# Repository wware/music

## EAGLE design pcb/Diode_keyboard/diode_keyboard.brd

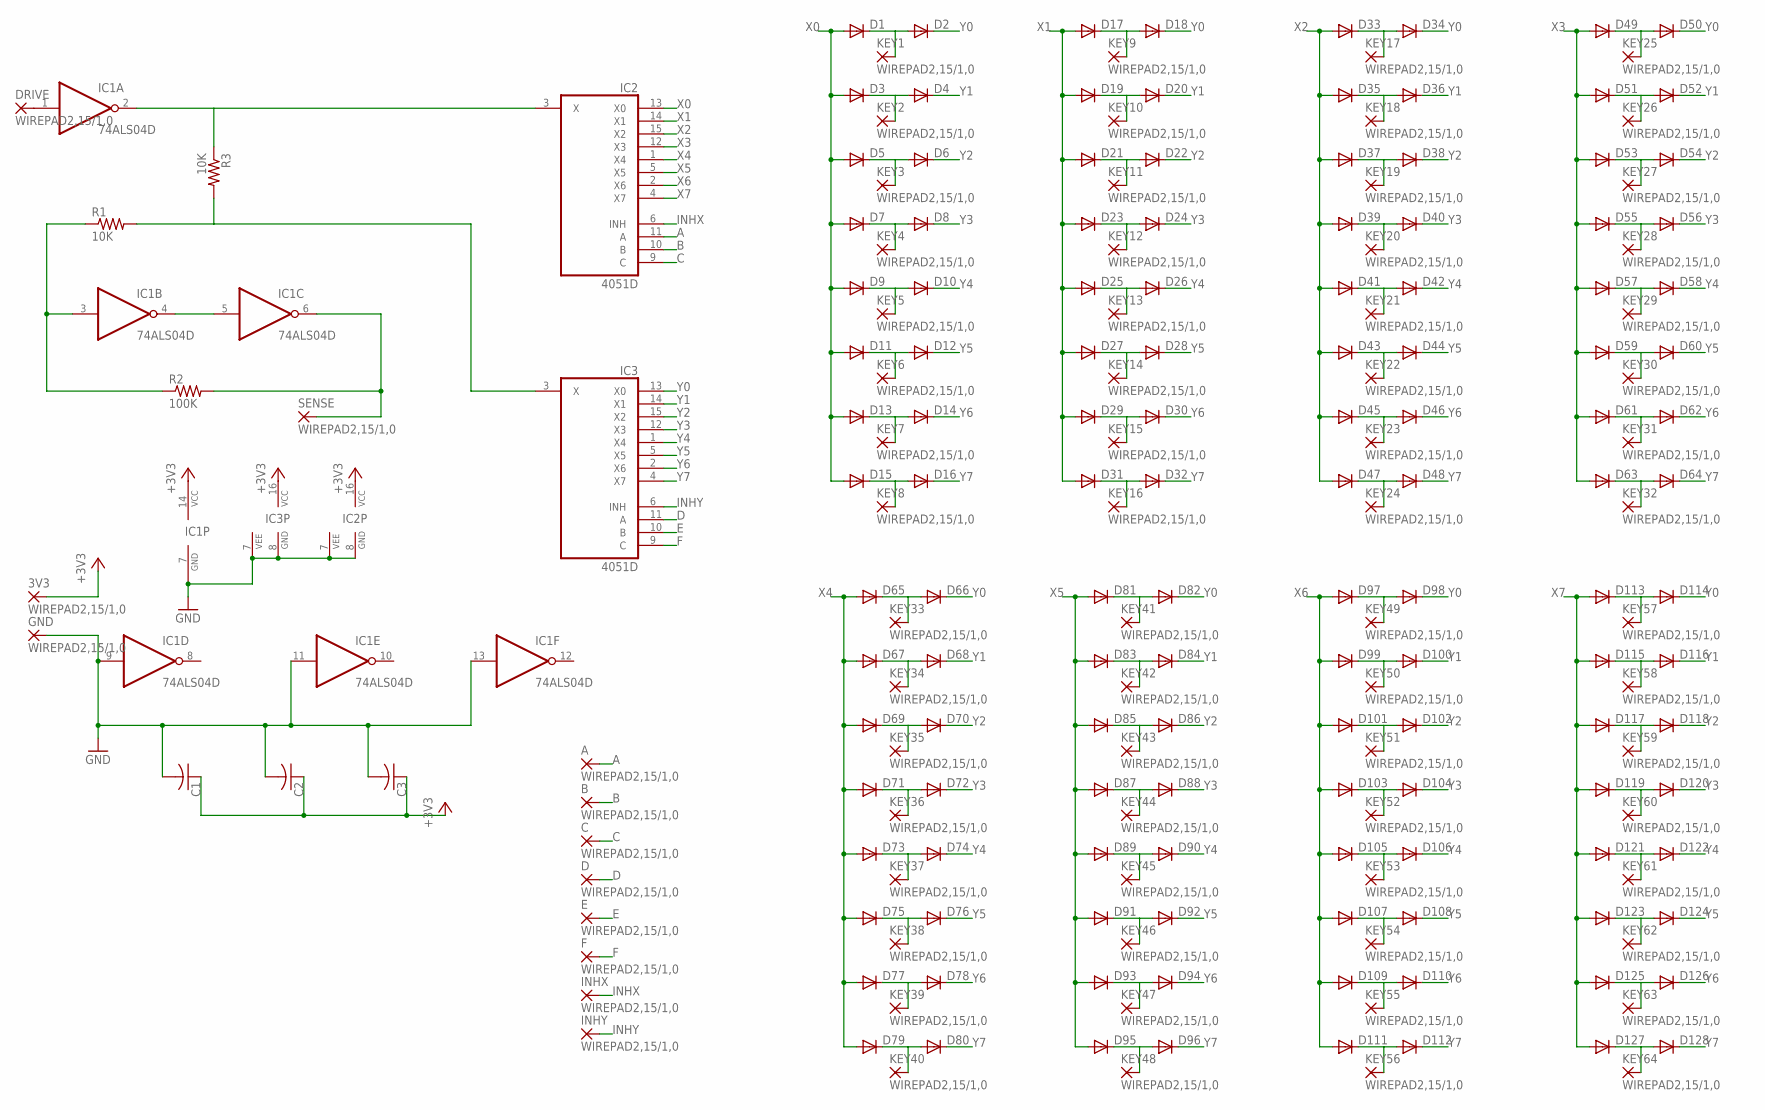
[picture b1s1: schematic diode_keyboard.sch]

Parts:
3V3: WIREPAD2,15/1,0; 2,15/1,0
A: WIREPAD2,15/1,0; 2,15/1,0
B: WIREPAD2,15/1,0; 2,15/1,0
C: WIREPAD2,15/1,0; 2,15/1,0
C1, C2, C3: C-US025-024X044; C025-024X044
D: WIREPAD2,15/1,0; 2,15/1,0
D1, D2, D3, D4, D5, D6, D7, D8, D9, D10, D11, D12, D13, D14, D15, D16, D17, D18, D19, D20, D21, D22, D23, D24, D25, D26, D27, D28, D29, D30, D31, D32, D33, D34, D35, D36, D37, D38, D39, D40, D41, D42, D43, D44, D45, D46, D47, D48, D49, D50, D51, D52, D53, D54, D55, D56, D57, D58, D59, D60, D61, D62, D63, D64, D65, D66, D67, D68, D69, D70, D71, D72, D73, D74, D75, D76, D77, D78, D79, D80, D81, D82, D83, D84, D85, D86, D87, D88, D89, D90, D91, D92, D93, D94, D95, D96, D97, D98, D99, D100, D101, D102, D103, D104, D105, D106, D107, D108, D109, D110, D111, D112, D113, D114, D115, D116, D117, D118, D119, D120, D121, D122, D123, D124, D125, D126, D127, D128: DIODE-D-2.5; D-2.5
DRIVE: WIREPAD2,15/1,0; 2,15/1,0
E: WIREPAD2,15/1,0; 2,15/1,0
F: WIREPAD2,15/1,0; 2,15/1,0
GND: WIREPAD2,15/1,0; 2,15/1,0
IC1: 74ALS04D; SO14
IC2, IC3: 4051D; SO16
INHX: WIREPAD2,15/1,0; 2,15/1,0
INHY: WIREPAD2,15/1,0; 2,15/1,0
KEY1, KEY2, KEY3, KEY4, KEY5, KEY6, KEY7, KEY8, KEY9, KEY10, KEY11, KEY12, KEY13, KEY14, KEY15, KEY16, KEY17, KEY18, KEY19, KEY20, KEY21, KEY22, KEY23, KEY24, KEY25, KEY26, KEY27, KEY28, KEY29, KEY30, KEY31, KEY32, KEY33, KEY34, KEY35, KEY36, KEY37, KEY38, KEY39, KEY40, KEY41, KEY42, KEY43, KEY44, KEY45, KEY46, KEY47, KEY48, KEY49, KEY50, KEY51, KEY52, KEY53, KEY54, KEY55, KEY56, KEY57, KEY58, KEY59, KEY60, KEY61, KEY62, KEY63, KEY64: WIREPAD2,15/1,0; 2,15/1,0
R1, R3: 10K; 0207/2V
R2: 100K; 0207/2V
SENSE: WIREPAD2,15/1,0; 2,15/1,0

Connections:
+3V3: 3V3.1, C1.1, C2.1, C3.1, IC1.14 (VCC), IC2.16 (VCC), IC3.16 (VCC)
A: A.1, IC2.11 (A)
B: B.1, IC2.10 (B)
C: C.1, IC2.9 (C)
D: D.1, IC3.11 (A)
E: E.1, IC3.10 (B)
F: F.1, IC3.9 (C)
GND: C1.2, C2.2, C3.2, GND.1, IC1.7 (GND), IC1.9 (I), IC1.11 (I), IC1.13 (I), IC2.7 (VEE), IC2.8 (GND), IC3.7 (VEE), IC3.8 (GND)
INHX: IC2.6 (INH), INHX.1
INHY: IC3.6 (INH), INHY.1
unnamed: IC1.4 (O), IC1.5 (I)
unnamed: IC1.3 (I), R1.1, R2.1
unnamed: IC3.3 (X), R1.2, R3.2
unnamed: IC1.2 (O), IC2.3 (X), R3.1
unnamed: IC1.6 (O), R2.2, SENSE.1
unnamed: D17.C, D18.A, KEY9.1
unnamed: DRIVE.1, IC1.1 (I)
unnamed: D1.C, D2.A, KEY1.1
unnamed: D19.C, D20.A, KEY10.1
unnamed: D3.C, D4.A, KEY2.1
unnamed: D5.C, D6.A, KEY3.1
unnamed: D21.C, D22.A, KEY11.1
unnamed: D23.C, D24.A, KEY12.1
unnamed: D7.C, D8.A, KEY4.1
unnamed: D25.C, D26.A, KEY13.1
unnamed: D27.C, D28.A, KEY14.1
unnamed: D9.C, D10.A, KEY5.1
unnamed: D29.C, D30.A, KEY15.1
unnamed: D31.C, D32.A, KEY16.1
unnamed: D11.C, D12.A, KEY6.1
unnamed: D33.C, D34.A, KEY17.1
unnamed: D35.C, D36.A, KEY18.1
unnamed: D13.C, D14.A, KEY7.1
unnamed: D37.C, D38.A, KEY19.1
unnamed: D15.C, D16.A, KEY8.1
unnamed: D39.C, D40.A, KEY20.1
unnamed: D41.C, D42.A, KEY21.1
unnamed: D43.C, D44.A, KEY22.1
unnamed: D45.C, D46.A, KEY23.1
unnamed: D47.C, D48.A, KEY24.1
unnamed: D49.C, D50.A, KEY25.1
unnamed: D51.C, D52.A, KEY26.1
unnamed: D53.C, D54.A, KEY27.1
unnamed: D55.C, D56.A, KEY28.1
unnamed: D57.C, D58.A, KEY29.1
unnamed: D59.C, D60.A, KEY30.1
unnamed: D61.C, D62.A, KEY31.1
unnamed: D63.C, D64.A, KEY32.1
unnamed: D65.C, D66.A, KEY33.1
unnamed: D67.C, D68.A, KEY34.1
unnamed: D69.C, D70.A, KEY35.1
unnamed: D71.C, D72.A, KEY36.1
unnamed: D73.C, D74.A, KEY37.1
unnamed: D75.C, D76.A, KEY38.1
unnamed: D77.C, D78.A, KEY39.1
unnamed: D79.C, D80.A, KEY40.1
unnamed: D81.C, D82.A, KEY41.1
unnamed: D83.C, D84.A, KEY42.1
unnamed: D85.C, D86.A, KEY43.1
unnamed: D87.C, D88.A, KEY44.1
unnamed: D89.C, D90.A, KEY45.1
unnamed: D91.C, D92.A, KEY46.1
unnamed: D93.C, D94.A, KEY47.1
unnamed: D95.C, D96.A, KEY48.1
unnamed: D97.C, D98.A, KEY49.1
unnamed: D99.C, D100.A, KEY50.1
unnamed: D101.C, D102.A, KEY51.1
unnamed: D103.C, D104.A, KEY52.1
unnamed: D105.C, D106.A, KEY53.1
unnamed: D107.C, D108.A, KEY54.1
unnamed: D109.C, D110.A, KEY55.1
unnamed: D111.C, D112.A, KEY56.1
unnamed: D113.C, D114.A, KEY57.1
unnamed: D115.C, D116.A, KEY58.1
unnamed: D117.C, D118.A, KEY59.1
unnamed: D119.C, D120.A, KEY60.1
unnamed: D121.C, D122.A, KEY61.1
unnamed: D123.C, D124.A, KEY62.1
unnamed: D125.C, D126.A, KEY63.1
unnamed: D127.C, D128.A, KEY64.1
X0: D1.A, D3.A, D5.A, D7.A, D9.A, D11.A, D13.A, D15.A, IC2.13 (X0)
X1: D17.A, D19.A, D21.A, D23.A, D25.A, D27.A, D29.A, D31.A, IC2.14 (X1)
X2: D33.A, D35.A, D37.A, D39.A, D41.A, D43.A, D45.A, D47.A, IC2.15 (X2)
X3: D49.A, D51.A, D53.A, D55.A, D57.A, D59.A, D61.A, D63.A, IC2.12 (X3)
X4: D65.A, D67.A, D69.A, D71.A, D73.A, D75.A, D77.A, D79.A, IC2.1 (X4)
X5: D81.A, D83.A, D85.A, D87.A, D89.A, D91.A, D93.A, D95.A, IC2.5 (X5)
X6: D97.A, D99.A, D101.A, D103.A, D105.A, D107.A, D109.A, D111.A, IC2.2 (X6)
X7: D113.A, D115.A, D117.A, D119.A, D121.A, D123.A, D125.A, D127.A, IC2.4 (X7)
Y0: D2.C, D18.C, D34.C, D50.C, D66.C, D82.C, D98.C, D114.C, IC3.13 (X0)
Y1: D4.C, D20.C, D36.C, D52.C, D68.C, D84.C, D100.C, D116.C, IC3.14 (X1)
Y2: D6.C, D22.C, D38.C, D54.C, D70.C, D86.C, D102.C, D118.C, IC3.15 (X2)
Y3: D8.C, D24.C, D40.C, D56.C, D72.C, D88.C, D104.C, D120.C, IC3.12 (X3)
Y4: D10.C, D26.C, D42.C, D58.C, D74.C, D90.C, D106.C, D122.C, IC3.1 (X4)
Y5: D12.C, D28.C, D44.C, D60.C, D76.C, D92.C, D108.C, D124.C, IC3.5 (X5)
Y6: D14.C, D30.C, D46.C, D62.C, D78.C, D94.C, D110.C, D126.C, IC3.2 (X6)
Y7: D16.C, D32.C, D48.C, D64.C, D80.C, D96.C, D112.C, D128.C, IC3.4 (X7)

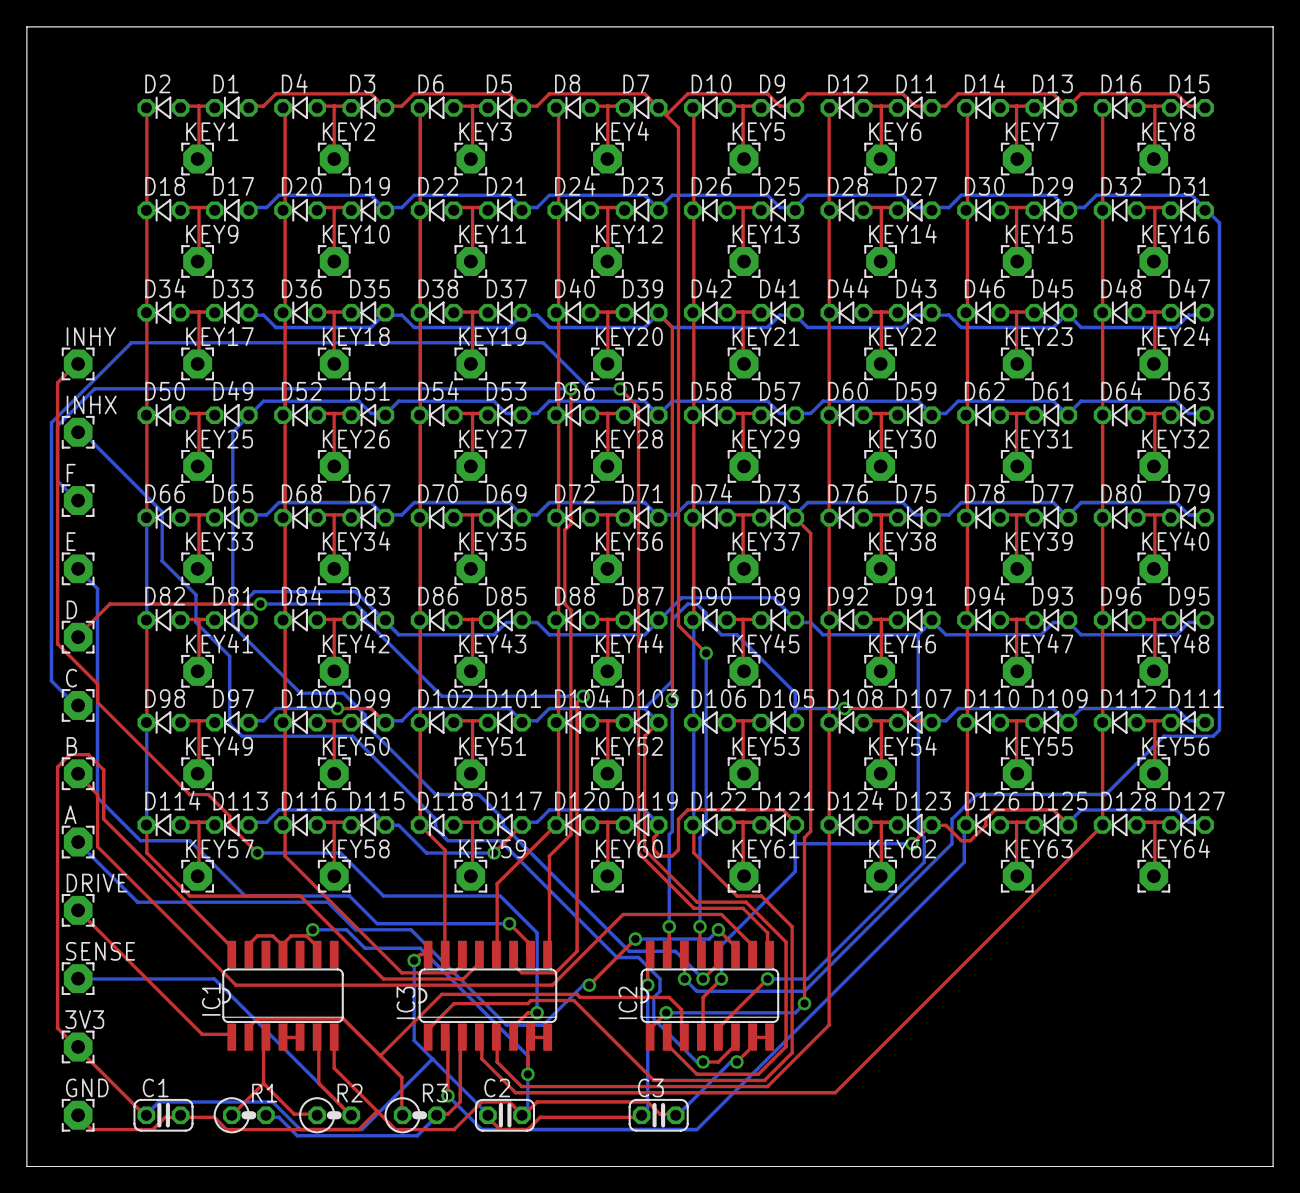
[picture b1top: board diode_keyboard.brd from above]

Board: 2 copper layers, 92.7 x 84.8 mm, 213 parts (0 on the bottom side), 96 nets.

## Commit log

2018-12-02 Here is the new thing.
2018-12-02 Hole needs to be smaller
2018-12-02 add a readme
2018-12-02 STL file for current design
2018-12-02 Don't gzip the STL
2018-12-02 some noodling
2018-12-04 two shells, 0.03 holes
2018-12-08 Add Eagle PCB stuff for 128-diode board
2018-12-08 after autorouter
